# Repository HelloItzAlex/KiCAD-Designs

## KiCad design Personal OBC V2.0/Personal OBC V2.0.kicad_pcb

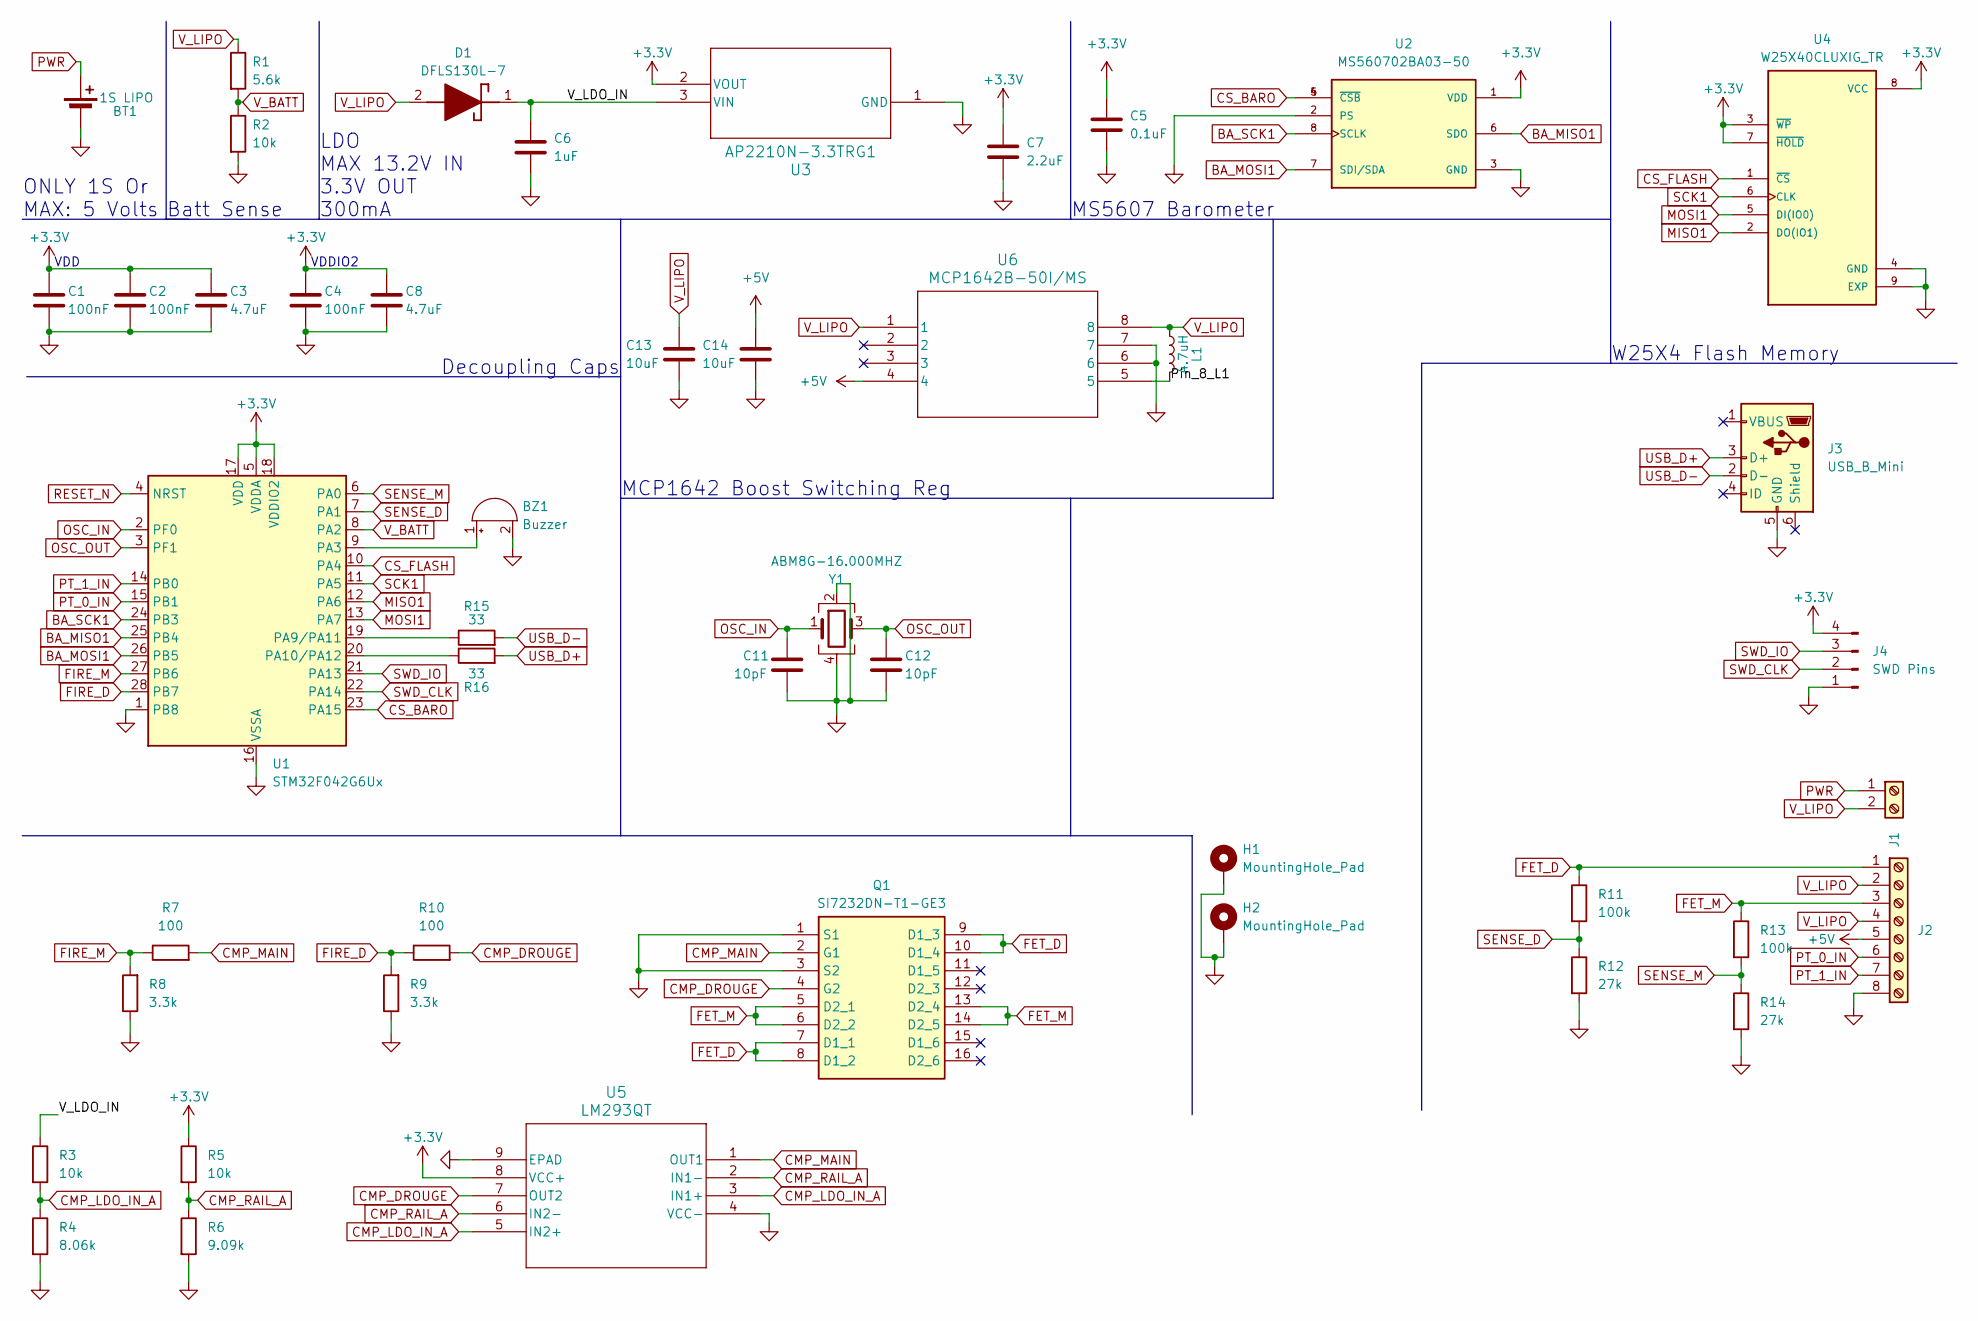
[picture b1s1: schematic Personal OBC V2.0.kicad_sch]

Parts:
BT1: 1S LIPO; JST_PH_B2B-PH-K_1x02_P2.00mm_Vertical
BZ1: Buzzer; Buzzer_TDK_PS1240P02BT_D12.2mm_H6.5mm
C1, C2, C4: 100nF; C_0402_1005Metric
C3, C8: 4.7uF; C_0402_1005Metric
C5: 0.1uF; C_0402_1005Metric
C6: 1uF; C_0402_1005Metric_Pad0.74x0.62mm_HandSolder
C7: 2.2uF; C_0402_1005Metric_Pad0.74x0.62mm_HandSolder
C11, C12: 10pF; C_0402_1005Metric
C13, C14: 10uF; C_0603_1608Metric_Pad1.08x0.95mm_HandSolder
D1: DFLS130L-7; DFLS130L7; Mouser Part Number 621-DFLS130L
H1, H2: MountingHole_Pad; MountingHole_3.2mm_M3_DIN965_Pad_TopOnly
J1: Screw_Terminal_01x02; 2_Pin_Conn
J2: Screw_Terminal_01x08; 8_Pin_Conn
J3: USB_B_Mini; USB_Micro-AB_Molex_47590-0001
J4: SWD Pins; 4_Pin_Conn
L1: 4.7uH; L_1008_2520Metric_Pad1.43x2.20mm_HandSolder
Q1: SI7232DN-T1-GE3; SI7232DNT1GE3; Mouser Part Number 781-SI7232DN-GE3
R1: 5.6k; R_0402_1005Metric
R2, R3, R5: 10k; R_0402_1005Metric
R4: 8.06k; R_0402_1005Metric
R6: 9.09k; R_0402_1005Metric
R7, R10: 100; R_0402_1005Metric
R8, R9: 3.3k; R_0402_1005Metric
R11, R13: 100k; R_0402_1005Metric
R12, R14: 27k; R_0402_1005Metric
R15, R16: 33; R_0402_1005Metric
U1: STM32F042G6Ux; QFN-28_4x4mm_P0.5mm
U2: MS560702BA03-50; SON125P300X500X100-8N
U3: AP2210N-3.3TRG1; SOT_3.3TRG1_DIO
U4: W25X40CLUXIG_TR; PSON50P300X200X60-9N; PARTREV F
U5: LM293QT; DFN8_2P16X2P16X0P5_STM
U6: MCP1642B-50I/MS; MSOP8_MCP1642B-50I&slash_MS_MCH-L
Y1: ABM8G-16.000MHZ; Crystal_SMD_Abracon_ABM8G-4Pin_3.2x2.5mm

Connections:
+3.3V: C1.1, C2.1, C3.1, C4.1, C5.1, C7.1, C8.1, J4.4, R5.1, U1.5 (VDDA), U1.17 (VDD), U1.18 (VDDIO2), U2.1 (VDD), U3.2 (VOUT), U4.3 (~WP), U4.7 (~HOLD), U4.8 (VCC), U5.8 (VCC+)
+5V: C14.1, J2.5, U6.4
/Pin_8_L1: L1.2, U6.5
/V_LDO_IN: C6.1, D1.1 (K), R3.1, U3.3 (VIN)
BA_MISO1: U1.25 (PB4), U2.6 (SDO)
BA_MOSI1: U1.26 (PB5), U2.7 (SDI/SDA)
BA_SCK1: U1.24 (PB3), U2.8 (SCLK)
CMP_DROUGE: Q1.4 (G2), R10.2, U5.7 (OUT2)
CMP_LDO_IN_A: R3.2, R4.1, U5.3 (IN1+), U5.5 (IN2+)
CMP_MAIN: Q1.2 (G1), R7.2, U5.1 (OUT1)
CMP_RAIL_A: R5.2, R6.1, U5.2 (IN1-), U5.6 (IN2-)
CS_BARO: U1.23 (PA15), U2.4 (~CSB), U2.5 (~CSB)
CS_FLASH: U1.10 (PA4), U4.1 (~CS)
FET_D: J2.1, Q1.7 (D1_1), Q1.8 (D1_2), Q1.9 (D1_3), Q1.10 (D1_4), R11.1
FET_M: J2.3, Q1.5 (D2_1), Q1.6 (D2_2), Q1.13 (D2_4), Q1.14 (D2_5), R13.1
FIRE_D: R9.2, R10.1, U1.28 (PB7)
FIRE_M: R7.1, R8.2, U1.27 (PB6)
GND: BT1.2 (-), BZ1.2 (+), C1.2, C2.2, C3.2, C4.2, C5.2, C6.2, C7.2, C8.2, C11.2, C12.2, C13.2, C14.2, H1.1, H2.1, J2.8, J3.5 (GND), J4.1, Q1.1 (S1), Q1.3 (S2), R2.2, R4.2, R6.2, R8.1, R9.1, R12.2, R14.2, U1.1 (PB8), U1.16 (VSSA), U2.2 (PS), U2.3 (GND), U3.1 (GND), U4.4 (GND), U4.9 (EXP), U5.4 (VCC-), U5.9 (EPAD), U6.6, U6.7, Y1.2, Y1.4; also elsewhere on the board
MISO1: U1.12 (PA6), U4.2 (DO(IO1))
MOSI1: U1.13 (PA7), U4.5 (DI(IO0))
unnamed: BZ1.1 (-), U1.9 (PA3)
unnamed: R15.1, U1.19 (PA9/PA11)
unnamed: R16.1, U1.20 (PA10/PA12)
OSC_IN: C11.1, U1.2 (PF0), Y1.1
OSC_OUT: C12.1, U1.3 (PF1), Y1.3
PT_0_IN: J2.6, U1.15 (PB1)
PT_1_IN: J2.7, U1.14 (PB0)
PWR: BT1.1 (+), J1.1; also elsewhere on the board
RESET_N: U1.4 (NRST)
SCK1: U1.11 (PA5), U4.6 (CLK)
SENSE_D: R11.2, R12.1, U1.7 (PA1)
SENSE_M: R13.2, R14.1, U1.6 (PA0)
SWD_CLK: J4.2, U1.22 (PA14)
SWD_IO: J4.3, U1.21 (PA13)
USB_D+: J3.3 (D+), R16.2
USB_D-: J3.2 (D-), R15.2
V_BATT: R1.2, R2.1, U1.8 (PA2)
V_LIPO: C13.1, D1.2 (A), J1.2, J2.2, J2.4, L1.1, R1.1, U6.1, U6.8

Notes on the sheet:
VDDIO2
MS5607 Barometer
LDO MAX 13.2V IN 3.3V OUT 300mA
W25X4 Flash Memory
Batt Sense
ONLY 1S Or MAX: 5 Volts
Decoupling Caps
VDD
MCP1642 Boost Switching Reg

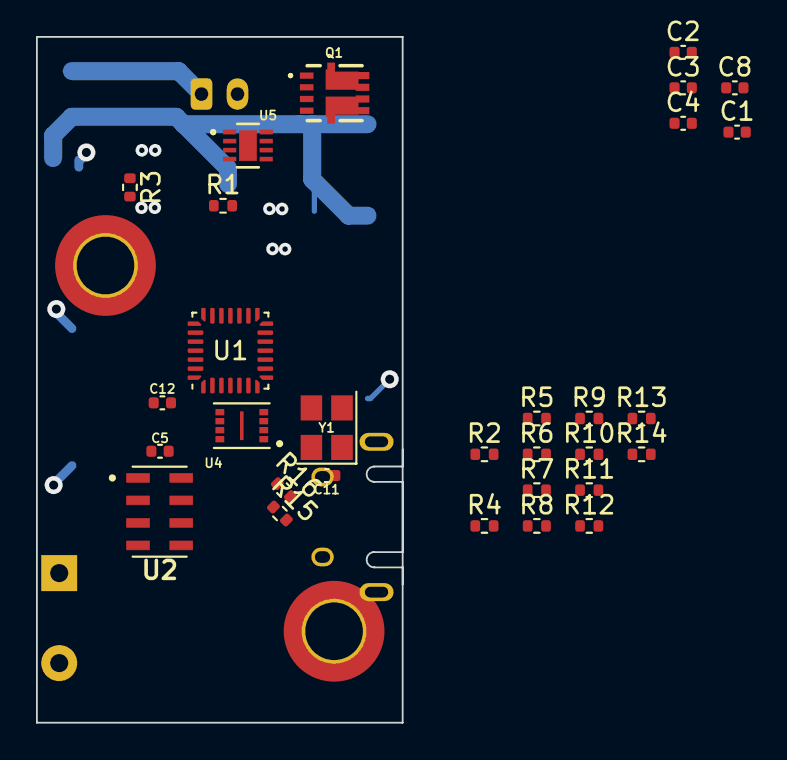
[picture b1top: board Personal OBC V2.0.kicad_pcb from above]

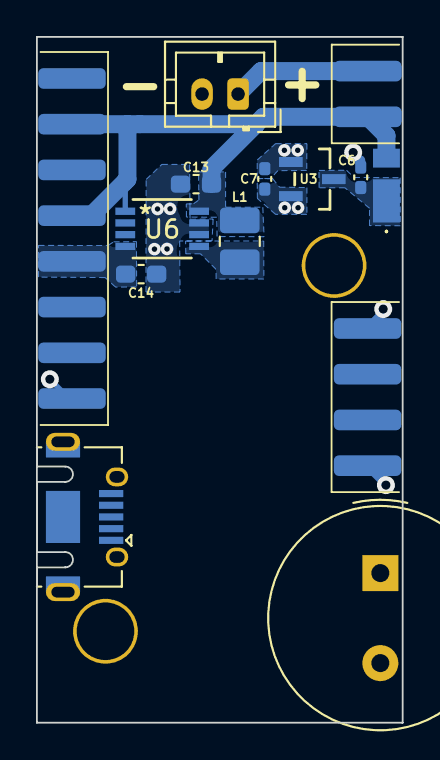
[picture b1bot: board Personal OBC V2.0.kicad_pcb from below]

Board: 4 copper layers, 20.3 x 38.1 mm, 46 parts (14 on the bottom side), 37 nets.

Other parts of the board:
BTr: 1S LIPO; JST_PH_B2B-PH-K_1x02_P2.00mm_Vertical

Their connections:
GND: BTr.2 (-); also elsewhere on the board
PWR: BTr.1 (+); also elsewhere on the board

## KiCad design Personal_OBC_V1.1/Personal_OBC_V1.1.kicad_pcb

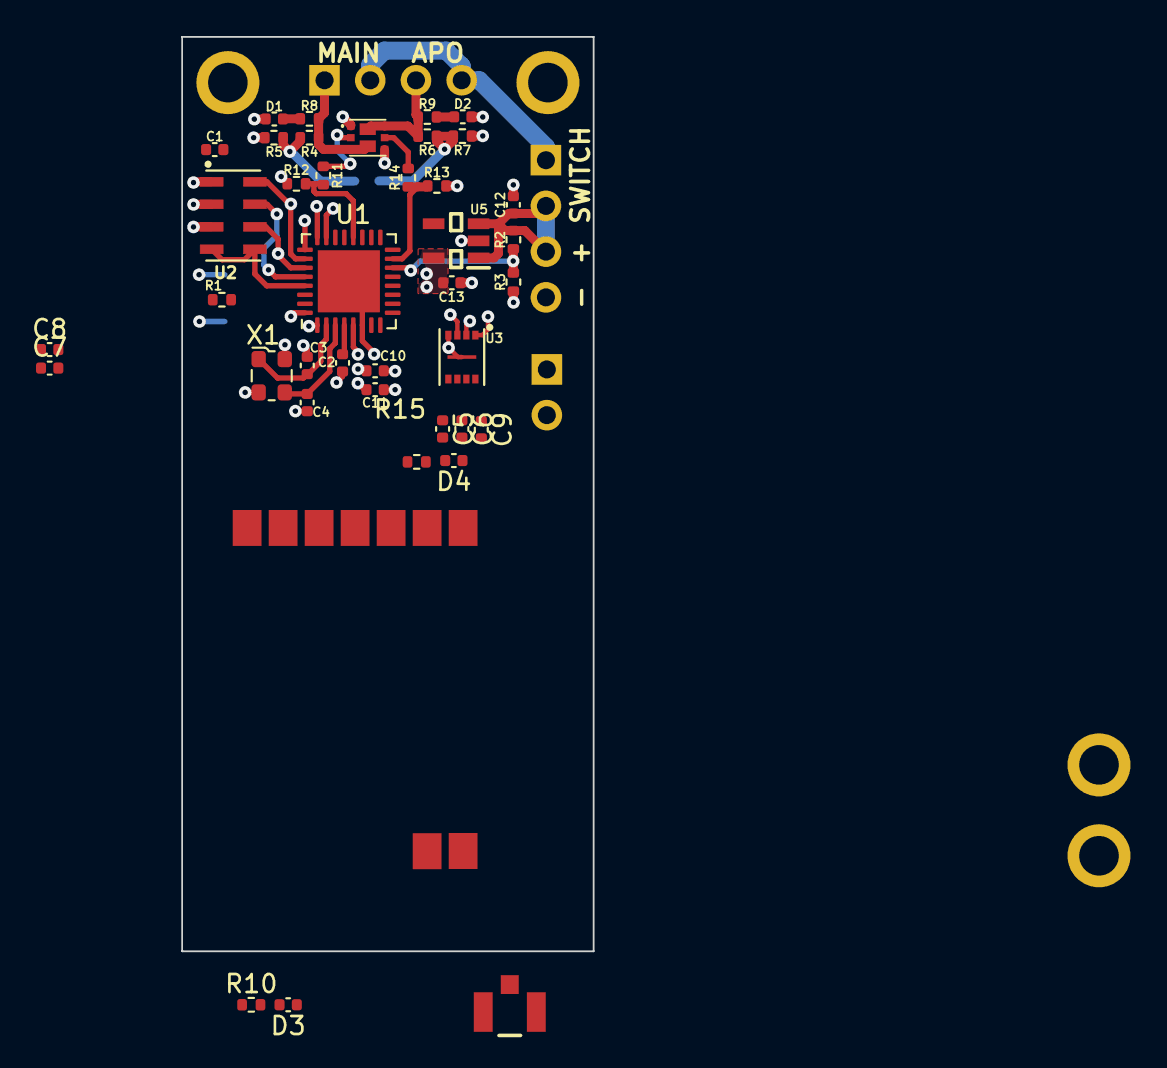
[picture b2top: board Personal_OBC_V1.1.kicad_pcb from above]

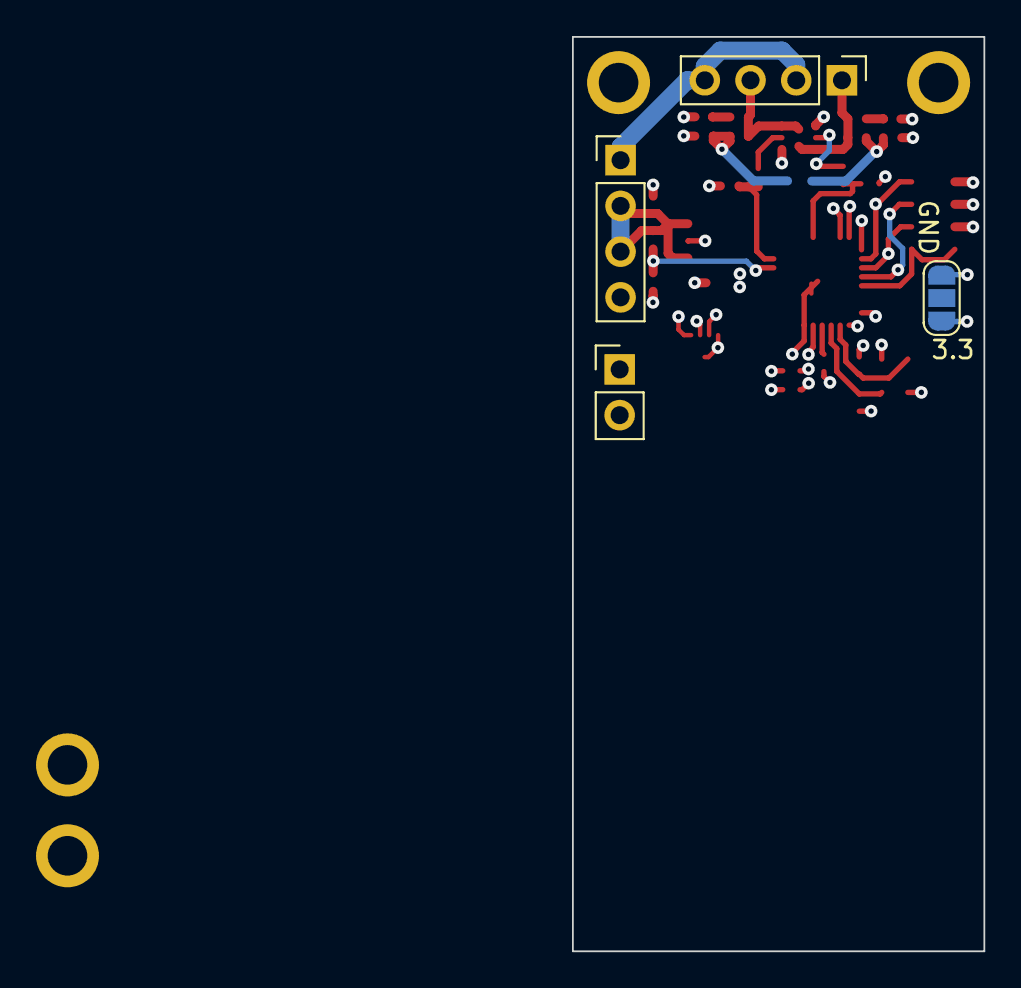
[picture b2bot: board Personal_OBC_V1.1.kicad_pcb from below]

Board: 4 copper layers, 22.9 x 50.8 mm, 48 parts (4 on the bottom side), 35 nets.

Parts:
C1, C5, C6, C7, C8: 100nF; C_0402_1005Metric
C2: 0.1uF; C_0402_1005Metric
C3, C4: 20pF; C_0402_1005Metric
C9: 4.7uF; C_0402_1005Metric
C10: 10nF; C_0402_1005Metric
C11: 1uF; C_0402_1005Metric
C12, C13: 1.0uF; C_0402_1005Metric
D1, D2: G_LED; C_0402_1005Metric
D3: R_LED; C_0402_1005Metric
D4: B_LED; C_0402_1005Metric
H1, H2, H3, H4: MountingHole_Pad; MountingHole_2.2mm_M2_ISO7380_Pad
J1: Conn_01x02_Pin; PinHeader_1x02_P2.54mm_Vertical
J2, J3: PROG PINS; PinHeader_1x04_P2.54mm_Vertical
J5: 636101111001
Q1: SSM6N58NU,LF; SSM6N58NULF
R1, R3: 10k; R_0402_1005Metric
R2: 5.6k; R_0402_1005Metric
R4, R6: 100k; R_0402_1005Metric
R5, R7: 27k; R_0402_1005Metric
R8, R9: 1k; R_0402_1005Metric
R10: 60; R_0402_1005Metric
R11, R14: 100; R_0402_1005Metric
R12, R13: 3.3k; R_0402_1005Metric
R15: 5; R_0402_1005Metric
SW1: SW_SPDT; SolderJumper-3_P1.3mm_Open_RoundedPad1.0x1.5mm_NumberLabels
U1: STM32F302K8Ux; QFN-32-1EP_5x5mm_P0.5mm_EP3.45x3.45mm
U2: MS560702BA03-50; SON125P300X500X100-8N
U3: W25X40CLUXIG_TR; PSON50P300X200X60-9N
U4: HM-TRPW
U5: AP2205-33W5-7; SOT95P282X130-5N
X1: ECS-2520MV-xxx-xx; Oscillator_SMD_ECS_2520MV-xxx-xx-4Pin_2.5x2.0mm

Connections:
+3.3V: C1.1, C5.1, C6.1, C7.1, C8.1, C9.1, C10.1, C11.1, C13.1, R10.1, SW1.3 (C), U1.1 (VDD), U1.5 (VDDA), U1.17 (VDD), U2.1 (VDD), U3.3 (~WP), U3.7 (~HOLD), U3.8 (VCC), U4.1 (VCC), U5.5 (VOUT)
BATT+: C12.1, J3.2, J3.3, R2.1, U5.1 (VIN), U5.3 (EN)
BOOT0: R1.1, U1.31 (BOOT0)
CONFIG: U1.8 (PA1), U4.5 (CONFIG)
CS_ALT: U1.29 (PB6), U2.4 (~CSB), U2.5 (~CSB)
CS_MEM: U1.25 (PA15), U3.1 (~CS)
ENABLE: U1.7 (PA0), U4.6 (ENABLE)
FET_APOGEE: J2.3, Q1.6 (D1_1), Q1.7 (D1_2), R6.1, R9.1
FET_MAIN: J2.1, Q1.3 (D2_1), Q1.8 (D2_2), R4.1, R8.1
FIRE_APOGEE: R11.1, R12.1, U1.20 (PA10)
FIRE_MAIN: R13.1, R14.1, U1.15 (PB0)
GND: C1.2, C2.1, C3.2, C4.2, C5.2, C6.2, C7.2, C8.2, C9.2, C10.2, C11.2, C12.2, C13.2, D1.1 (K), D2.1 (K), D3.1 (K), D4.1 (K), H1.1, H2.1, H3.1, H4.1, J3.4, J5.1, J5.3, Q1.1 (S1), Q1.4 (S2), R3.2, R5.2, R7.2, R12.2, R13.2, SW1.1 (A), U1.6 (VSSA), U1.16 (VSS), U1.32 (VSS), U1.33 (VSS), U2.2 (PS), U2.3 (GND), U3.4 (GND), U3.9 (EXP), U4.3 (GND), U4.9 (GND), U5.2 (GND), X1.2 (GND), X1.4 (VDD)
LED_1: R15.1, U1.11 (PA4)
MISO: U1.27 (PB4), U2.6 (SDO), U3.2 (DO(IO1))
MOSI: U1.28 (PB5), U2.7 (SDI/SDA), U3.5 (DI(IO0))
unnamed: D1.2 (A), R8.2
unnamed: D2.2 (A), R9.2
unnamed: D3.2 (A), R10.2
unnamed: D4.2 (A), R15.2
unnamed: Q1.2 (G1), R11.2
unnamed: Q1.5 (G2), R14.2
unnamed: R1.2, SW1.2 (B)
unnamed: C2.2, U1.4 (NRST)
PWR+: J2.2, J2.4, J3.1
RCC_OSC_IN: C3.1, U1.2 (PF0), X1.1 (Tri-State)
RCC_OSC_OUT: C4.1, U1.3 (PF1), X1.3 (OUT)
SCLK: U1.26 (PB3), U2.8 (SCLK), U3.6 (CLK)
SENSE_APOGEE: R6.2, R7.1, U1.18 (PA8)
SENSE_MAIN: R4.2, R5.1, U1.19 (PA9)
SYS_SWCLK: J1.2, U1.24 (PA14)
SYS_SWDIO: J1.1, U1.23 (PA13)
TO_ANT: J5.2, U4.8 (ANT)
USART_RX: U1.10 (PA3), U4.4 (DRX)
USART_TX: U1.9 (PA2), U4.2 (DTX)
V_BAT: R2.2, R3.1, U1.14 (PA7)

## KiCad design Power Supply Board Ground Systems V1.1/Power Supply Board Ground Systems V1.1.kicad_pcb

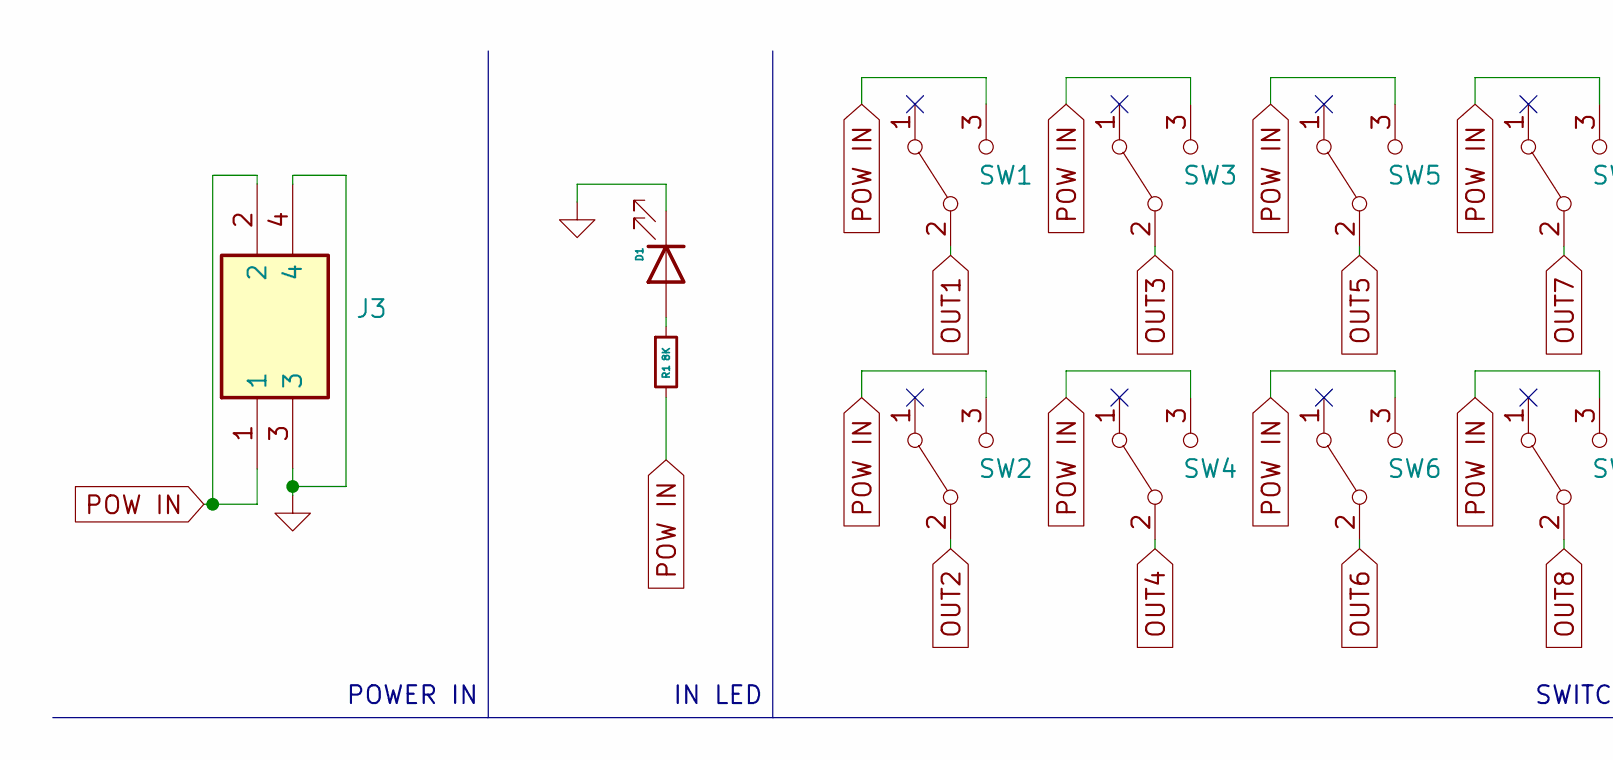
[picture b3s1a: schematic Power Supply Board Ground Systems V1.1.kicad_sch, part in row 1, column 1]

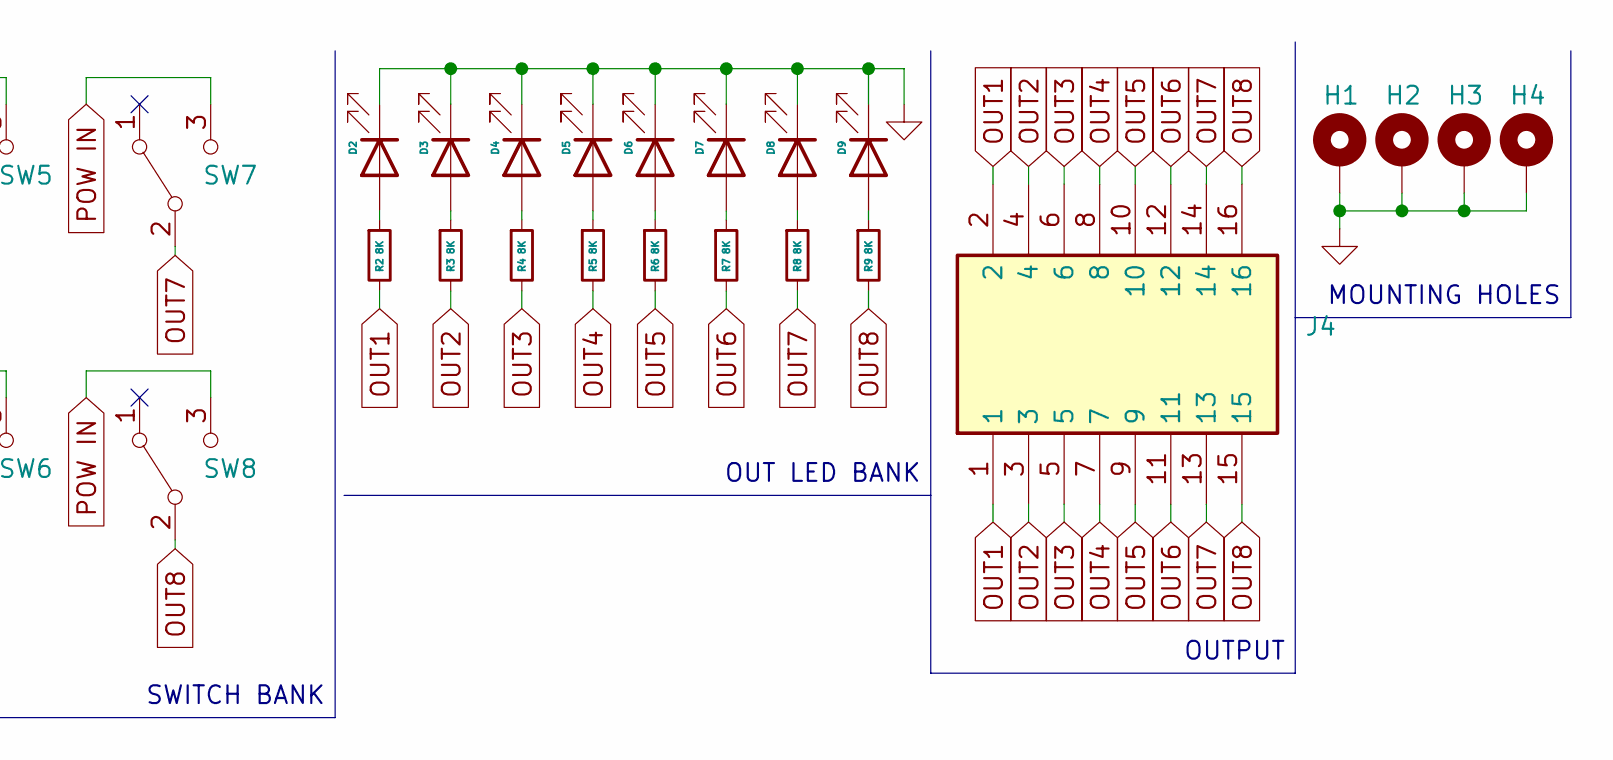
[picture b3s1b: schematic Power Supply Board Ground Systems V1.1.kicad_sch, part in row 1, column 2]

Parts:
D1, D2, D3, D4, D5, D6, D7, D8, D9: LED; LED_0805_2012Metric
H1, H2, H3, H4: MountingHole_Pad; MountingHole_3.2mm_M3_Pad_TopBottom
J3: TBLH10V-350-02BK; RHDR4W80P550X350_2X2_770X850X1420P; Mouser Part Number 490-TBLH10V-350-02BK
J4: TBLH10V-350-08BK; RHDR16W80P550X350_2X8_2870X850X1420P; Mouser Part Number 490-TBLH10V-350-08BK
R1, R2, R3, R4, R5, R6, R7, R8, R9: 8K; R_0603_1608Metric
SW1, SW2, SW3, SW4, SW5, SW6, SW7, SW8: SW_SPDT; 100SP1T1B1M2QEH

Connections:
GND: D1.1 (K), D2.1 (K), D3.1 (K), D4.1 (K), D5.1 (K), D6.1 (K), D7.1 (K), D8.1 (K), D9.1 (K), H1.1, H2.1, H3.1, H4.1, J3.3, J3.4
unnamed: D1.2 (A), R1.1
unnamed: D2.2 (A), R2.1
unnamed: D3.2 (A), R3.1
unnamed: D4.2 (A), R4.1
unnamed: D5.2 (A), R5.1
unnamed: D6.2 (A), R6.1
unnamed: D7.2 (A), R7.1
unnamed: D8.2 (A), R8.1
unnamed: D9.2 (A), R9.1
OUT1: J4.1, J4.2, R2.2, SW1.2 (B)
OUT2: J4.3, J4.4, R3.2, SW2.2 (B)
OUT3: J4.5, J4.6, R4.2, SW3.2 (B)
OUT4: J4.7, J4.8, R5.2, SW4.2 (B)
OUT5: J4.9, J4.10, R6.2, SW5.2 (B)
OUT6: J4.11, J4.12, R7.2, SW6.2 (B)
OUT7: J4.13, J4.14, R8.2, SW7.2 (B)
OUT8: J4.15, J4.16, R9.2, SW8.2 (B)
POW IN: J3.1, J3.2, R1.2, SW1.3 (C), SW2.3 (C), SW3.3 (C), SW4.3 (C), SW5.3 (C), SW6.3 (C), SW7.3 (C), SW8.3 (C)

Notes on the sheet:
SWITCH BANK
POWER IN
OUT LED BANK
IN LED
MOUNTING HOLES
OUTPUT

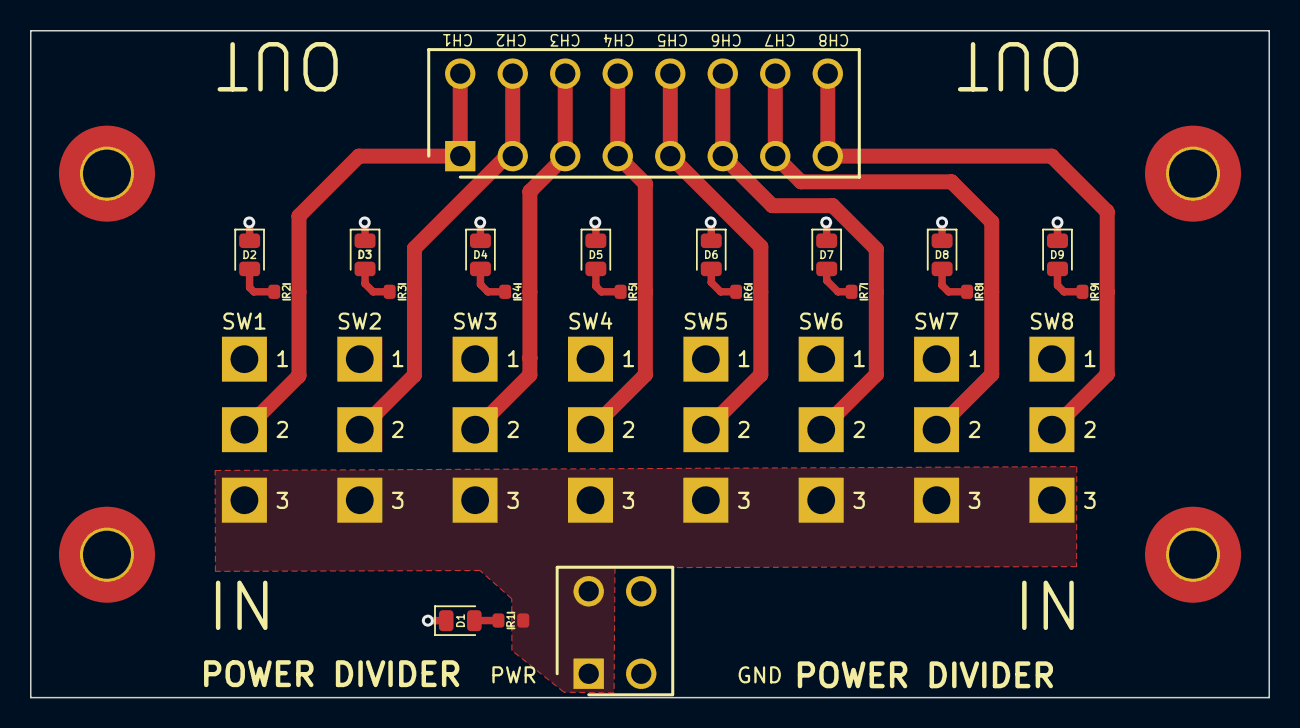
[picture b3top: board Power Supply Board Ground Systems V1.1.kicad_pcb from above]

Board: 2 copper layers, 82.6 x 44.4 mm, 32 parts (0 on the bottom side), 19 nets.

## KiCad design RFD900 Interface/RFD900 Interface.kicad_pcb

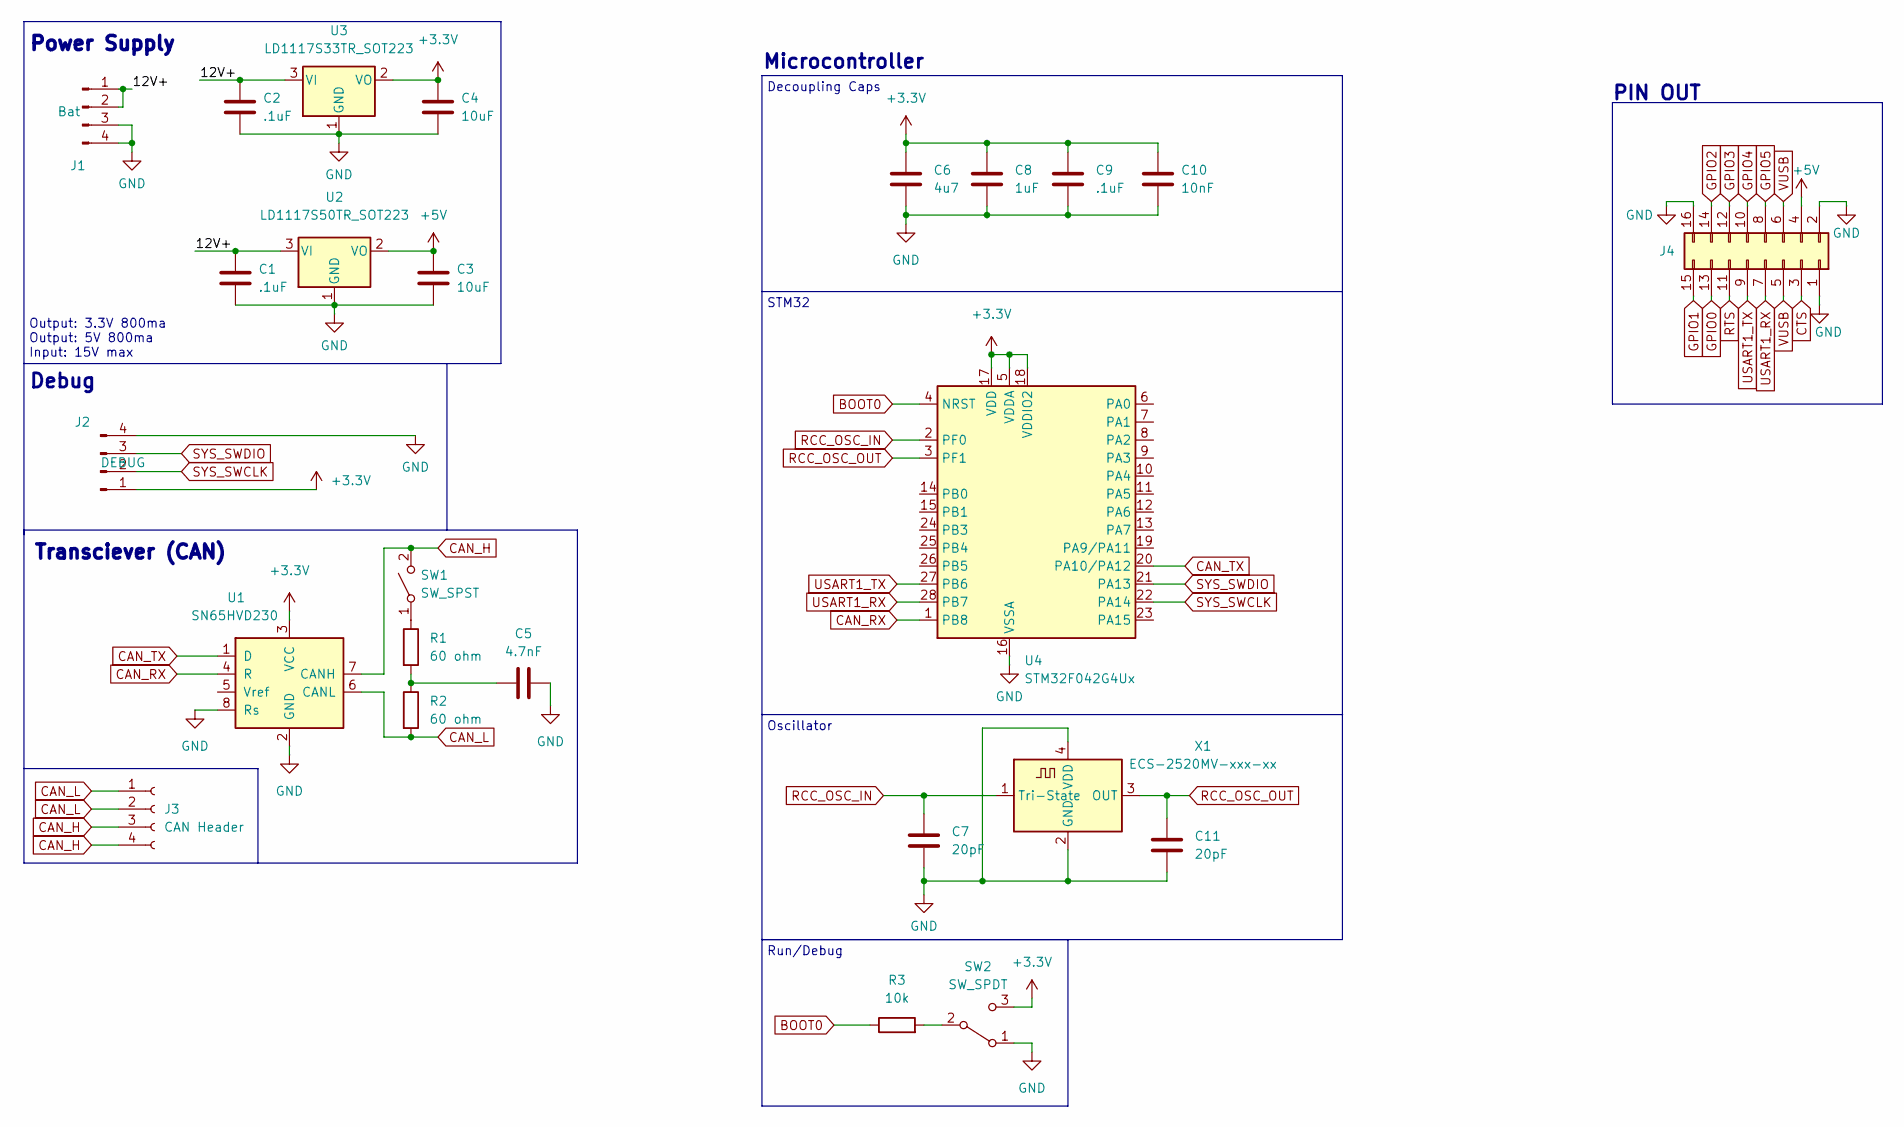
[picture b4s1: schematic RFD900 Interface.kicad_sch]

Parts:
C1, C2, C9: .1uF; C_0402_1005Metric
C3, C4: 10uF; C_0603_1608Metric
C5: 4.7nF; C_0402_1005Metric
C6: 4u7; C_0402_1005Metric
C7, C11: 20pF; C_0402_1005Metric
C8: 1uF; C_0402_1005Metric
C10: 10nF; C_0402_1005Metric
J1: Bat; PinHeader_1x04_P2.54mm_Vertical
J2: DEBUG; PinHeader_1x04_P2.54mm_Vertical
J3: CAN Header; PinHeader_1x04_P2.54mm_Vertical
J4: Conn_02x08_Odd_Even; PinSocket_2x08_P2.54mm_Horizontal
R1, R2: 60 ohm; R_0805_2012Metric
R3: 10k; R_0402_1005Metric
SW1: SW_SPST; SolderJumper-2_P1.3mm_Open_RoundedPad1.0x1.5mm
SW2: SW_SPDT; SolderJumper-3_P1.3mm_Open_RoundedPad1.0x1.5mm_NumberLabels
U1: SN65HVD230; SOIC-8_3.9x4.9mm_P1.27mm
U2: LD1117S50TR_SOT223; SOT-223-3_TabPin2
U3: LD1117S33TR_SOT223; SOT-223-3_TabPin2
U4: STM32F042G4Ux; QFN-28_4x4mm_P0.5mm
X1: ECS-2520MV-xxx-xx; Oscillator_SMD_ECS_2520MV-xxx-xx-4Pin_2.5x2.0mm

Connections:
+3.3V: C4.1, C6.1, C8.1, C9.1, C10.1, J2.1, SW2.3 (C), U1.3 (VCC), U3.2 (VO), U4.5 (VDDA), U4.17 (VDD), U4.18 (VDDIO2)
+5V: C3.1, J4.4, U2.2 (VO)
/12V+: C1.1, C2.1, J1.1, J1.2, U2.3 (VI), U3.3 (VI)
BOOT0: R3.1, U4.4 (NRST)
CAN_H: J3.3, J3.4, SW1.2 (B), U1.7 (CANH)
CAN_L: J3.1, J3.2, R2.2, U1.6 (CANL)
CAN_RX: U1.4 (R), U4.1 (PB8)
CAN_TX: U1.1 (D), U4.20 (PA10/PA12)
CTS: J4.3
GND: C1.2, C2.2, C3.2, C4.2, C5.2, C6.2, C7.2, C8.2, C9.2, C10.2, C11.2, J1.3, J1.4, J2.4, J4.1, J4.2, J4.16, SW2.1 (A), U1.2 (GND), U1.8 (Rs), U2.1 (GND), U3.1 (GND), U4.16 (VSSA), X1.2 (GND), X1.4 (VDD)
GPIO0: J4.13
GPIO1: J4.15
GPIO2: J4.14
GPIO3: J4.12
GPIO4: J4.10
GPIO5: J4.8
unnamed: C5.1, R1.2, R2.1
unnamed: R1.1, SW1.1 (A)
unnamed: R3.2, SW2.2 (B)
RCC_OSC_IN: C7.1, U4.2 (PF0), X1.1 (Tri-State)
RCC_OSC_OUT: C11.1, U4.3 (PF1), X1.3 (OUT)
RTS: J4.11
SYS_SWCLK: J2.2, U4.22 (PA14)
SYS_SWDIO: J2.3, U4.21 (PA13)
USART1_RX: J4.7, U4.28 (PB7)
USART1_TX: J4.9, U4.27 (PB6)
VUSB: J4.5, J4.6

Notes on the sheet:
Decoupling Caps
Run/Debug
Transciever (CAN)
Debug
PIN OUT
Oscillator
Power Supply
Microcontroller
Output: 3.3V 800ma Output: 5V 800ma Input: 15V max
STM32

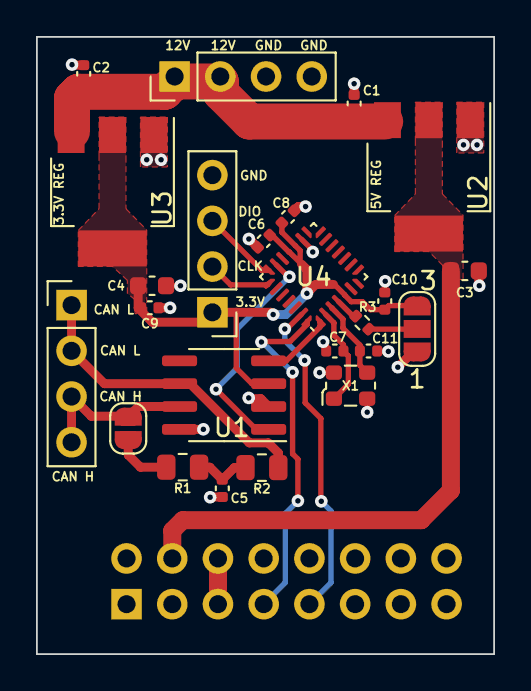
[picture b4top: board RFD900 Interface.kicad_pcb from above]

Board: 2 copper layers, 25.4 x 34.3 mm, 25 parts (1 on the bottom side), 19 nets.

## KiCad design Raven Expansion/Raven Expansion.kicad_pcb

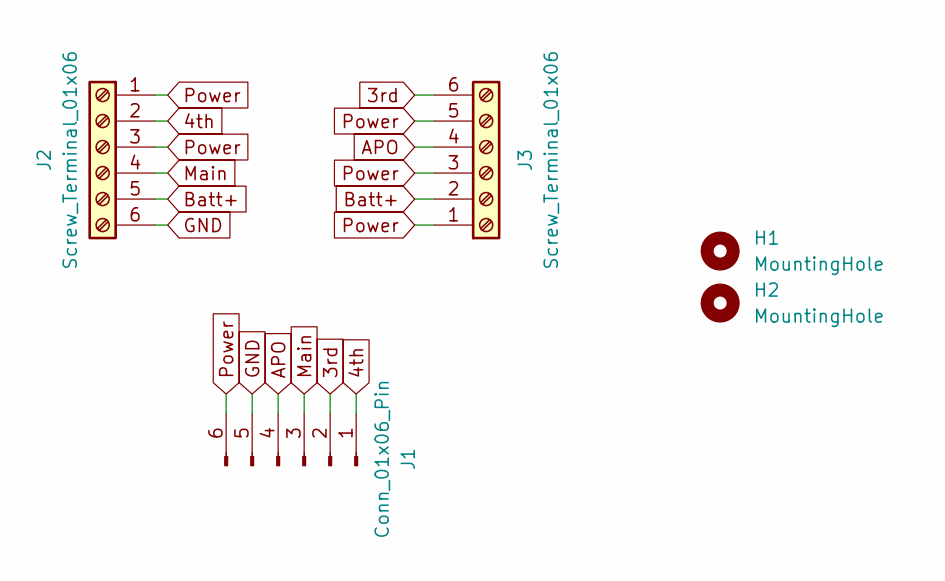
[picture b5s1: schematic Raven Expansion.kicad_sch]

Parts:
H1, H2: MountingHole; MountingHole_3.2mm_M3
J1: Conn_01x06_Pin; PinHeader_1x06_P2.54mm_Horizontal
J2, J3: Screw_Terminal_01x06; TerminalBlock_Phoenix_PT-1,5-6-3.5-H_1x06_P3.50mm_Horizontal

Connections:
3rd: J1.2, J3.6
4th: J1.1, J2.2
APO: J1.4, J3.4
Batt+: J2.5, J3.2
GND: J1.5, J2.6
Main: J1.3, J2.4
Power: J1.6, J2.1, J2.3, J3.1, J3.3, J3.5

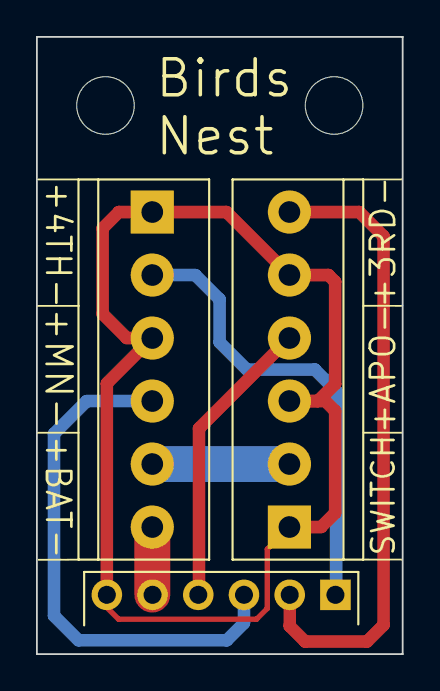
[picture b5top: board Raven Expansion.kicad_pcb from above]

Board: 2 copper layers, 20.3 x 34.3 mm, 5 parts (0 on the bottom side), 7 nets.

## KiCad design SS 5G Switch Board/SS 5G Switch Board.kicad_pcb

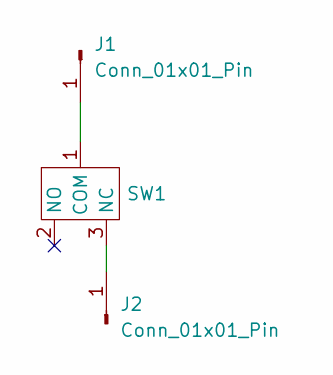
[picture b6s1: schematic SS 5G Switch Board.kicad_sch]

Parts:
J1, J2: Conn_01x01_Pin; SolderWire-0.75sqmm_1x01_D1.25mm_OD3.5mm_Relief
SW1: SS-5G

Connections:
unnamed: J1.1, SW1.1 (COM)
unnamed: J2.1, SW1.3 (NC)

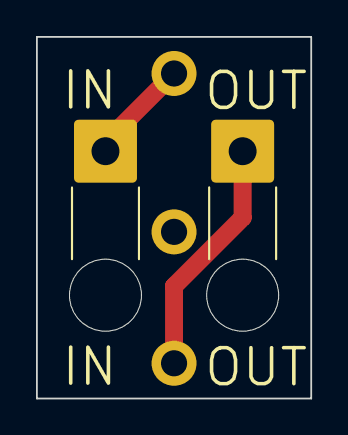
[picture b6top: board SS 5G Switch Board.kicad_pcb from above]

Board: 2 copper layers, 15.2 x 20.1 mm, 3 parts (0 on the bottom side), 2 nets.
